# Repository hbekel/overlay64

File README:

overlay64 - video overlay module

The overlay64 module allows superimposing predefined texts onto an
existing composite signal or onto the luminance portion of an s-video
signal depending on the states of up to sixteen digital input
lines. An LM1881 video sync separator IC is used to detect the
vertical and horizontal sync pulses of the video signal. An Atmega1284
uses these signals to synchronize with the video signal and to
superimpose text on the video display by bit-banging the corresponding
characters over SPI.

The user writes a simple configuration file that determines which
texts are to be displayed for which input line states. The
configuration file is converted to a binary format using the supplied
commandline tool before flashing it to the Atmegas's eeprom memory via
the USB interface.

Possible uses include displaying the state of control lines for
additional hardware installed in a homecomputer such as the Commodore
64, for example to display the currently selected kernal based on the
state of the control lines for a multi-kernal adapter.

An early working prototype can be seen in this video where it displays
the runtime configuration of the MixSID Stereo SID board:

https://www.youtube.com/watch?v=0exp2yM0WHM

This repository includes the complete sourcecode of the client
software, the firmware and all design files in KiCAD format.

LICENSING

Hardware licenced under CERN OHL v.1.2, see ./hardware/LICENSE.txt
Software and firmware licenced under GNU GPLv3, see ./LICENSE

The software contains MIT licensed code from
https://github.com/arkku/ihex for reading Intel HEX files, Copyright
(c) 2013-2015 Kimmo Kulovesi, see ./intelhex/LICENSE

The firmware contains the V-USB Driver (https://www.obdev.at/vusb),
(C)2008 Objective Development GmbH.

Distributed in the ./bootloader directory is the USBasp bootloader,
(C)2013 Stephan Baerwolf (matrixstorm@gmx.de) and (C)2008 Objective
Development GmbH (https://www.obdev.at/vusb).

In compliance with the terms of the (identical) V-USB driver and
USBasp bootloader licenses (./firmware/usbdrv/License.txt and
./bootloader/License.txt), the entire project is published under

http://www.henning-bekel.de/overlay64

In addition, this distribution contains

- a circuit diagram in PDF format, see ./hardware/overlay64-schematics.pdf
- the full source code for the host software in ./firmware
- this README file
- references to https://www.obdev.at/vusb

The USB Product and Vendor IDs for the Overlay64 USB device have kindly
been provided by OpenMoko, Inc (http://openmoko.org).

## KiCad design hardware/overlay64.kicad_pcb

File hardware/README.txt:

Overlay64 Rev.1 -- Video Overlay Module
Copyright Henning Bekel 2016.
Licensed under CERN OSH v.1.2 (see LICENSE.pdf)

This directory contains hardware documentation (as defined by the
terms of the CERN OSH v.1.2) for the Overlay64, a simple programmable
video overlay module. For more information, please visit

http://www.henning-bekel.de/overlay64

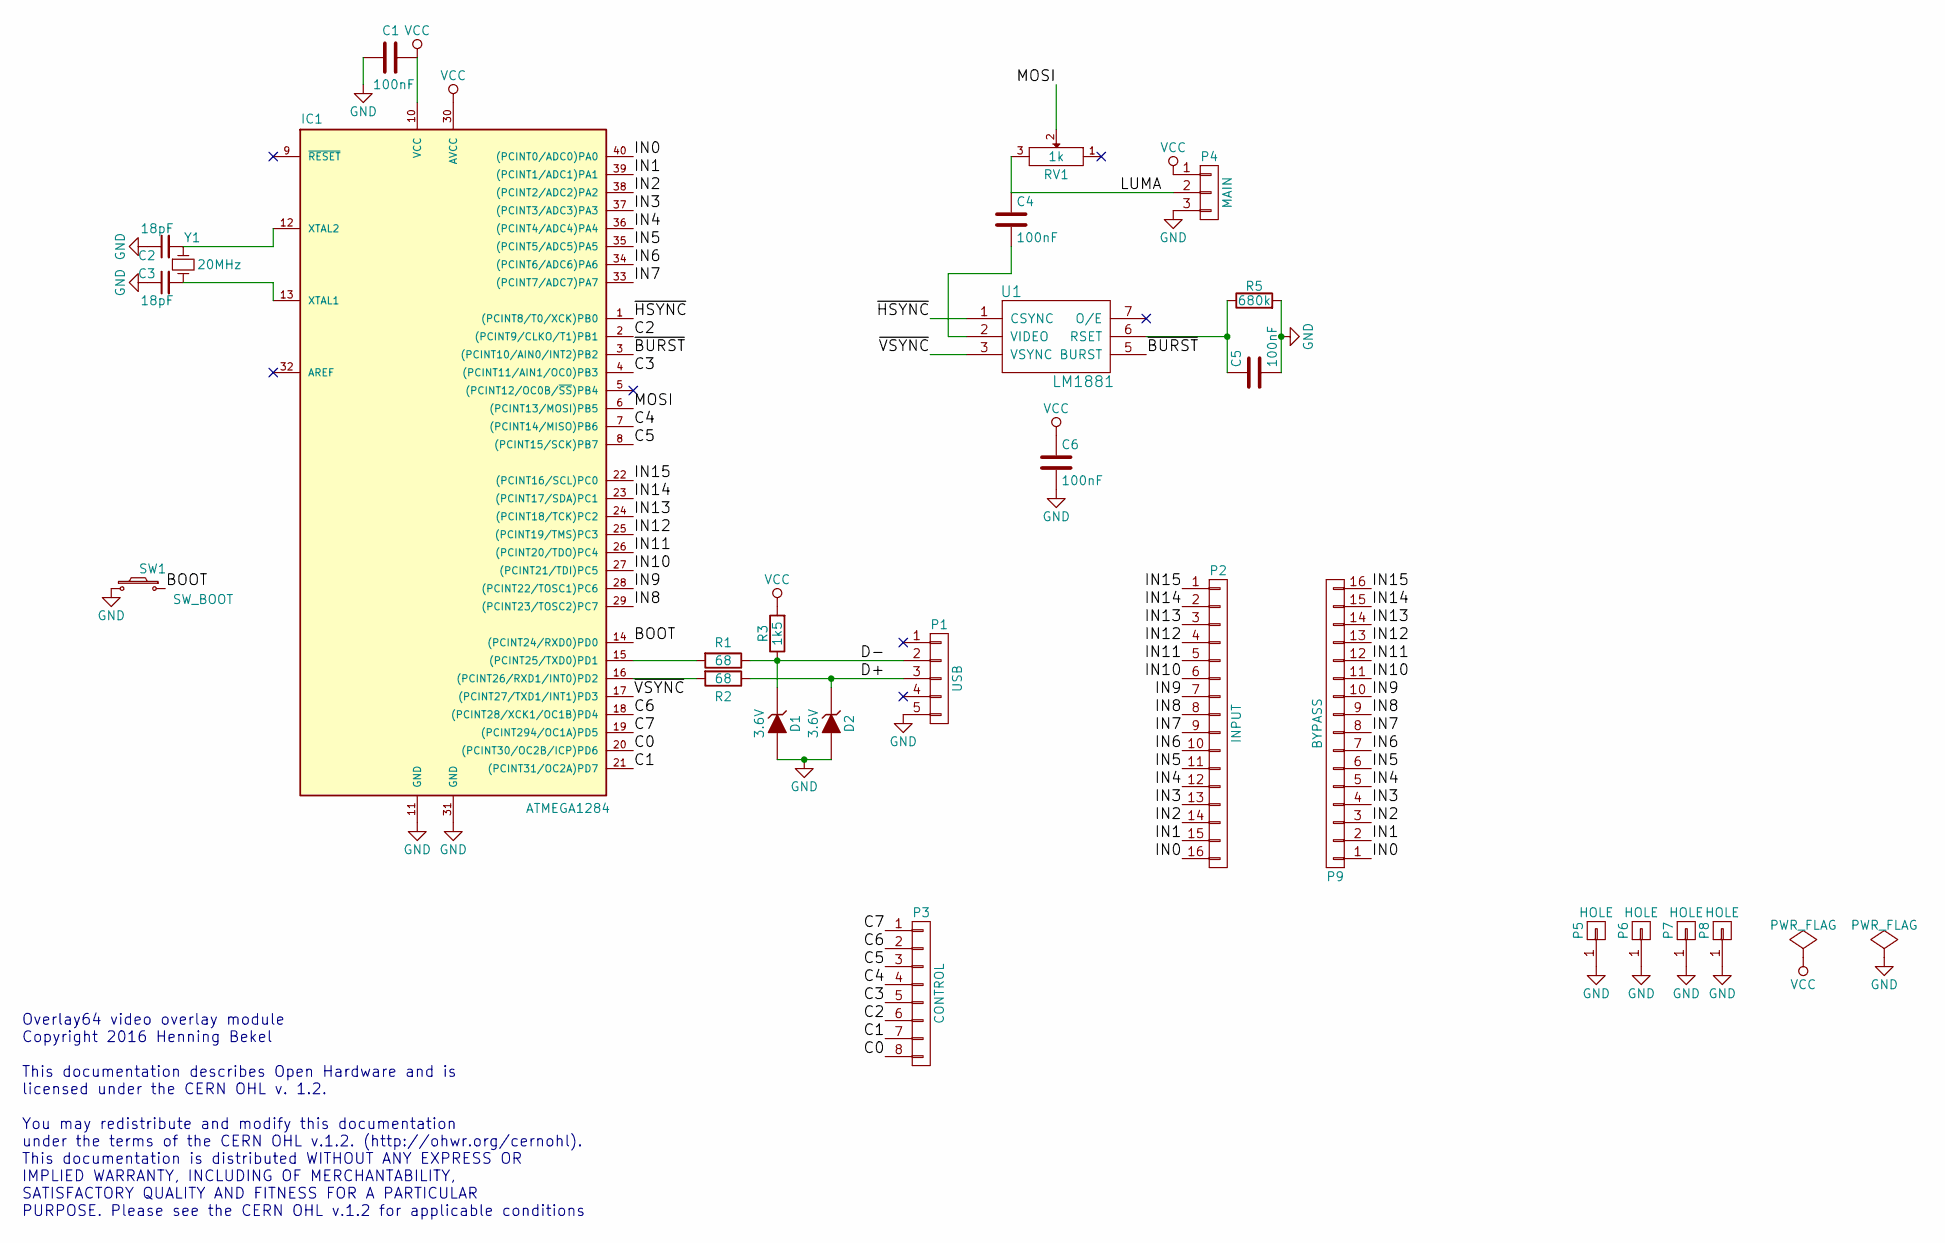
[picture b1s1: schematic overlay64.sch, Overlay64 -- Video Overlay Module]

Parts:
C1, C4, C5, C6: 100nF; C_Disc_D3_P2.5
C2, C3: 18pF; C_Disc_D3_P2.5
D1, D2: 3.6V; D3
IC1: ATMEGA1284; DIP-40_W15.24mm
P1: USB; USB-MINI-B-TH
P2: INPUT; Pin_Header_Angled_1x16
P3: CONTROL; Pin_Header_Angled_1x08
P4: MAIN; Pin_Header_Angled_1x03
P5, P6, P7, P8: HOLE; MountingHole_4mm
P9: BYPASS; Pin_Header_Angled_1x16
R1, R2: 68; R3
R3: 1k5; R3
R5: 680k; R3
RV1: 1k; Potentiometer_Bourns_3339P_Angular_ScrewUp
SW1: SW_BOOT; Button
U1: LM1881; DIP-8_W7.62mm
Y1: 20MHz; Crystal_HC49-U_Vertical

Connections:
/BOOT: IC1.14 ((PCINT24/RXD0)PD0), SW1.2
/C0: IC1.20 ((PCINT30/OC2B/ICP)PD6), P3.8
/C1: IC1.21 ((PCINT31/OC2A)PD7), P3.7
/C2: IC1.2 ((PCINT9/CLKO/T1)PB1), P3.6
/C3: IC1.4 ((PCINT11/AIN1/OC0)PB3), P3.5
/C4: IC1.7 ((PCINT14/MISO)PB6), P3.4
/C5: IC1.8 ((PCINT15/SCK)PB7), P3.3
/C6: IC1.18 ((PCINT28/XCK1/OC1B)PD4), P3.2
/C7: IC1.19 ((PCINT294/OC1A)PD5), P3.1
/D+: D2.1 (K), P1.3, R2.1
/D-: D1.1 (K), P1.2, R1.1, R3.1
/IN0: IC1.40 ((PCINT0/ADC0)PA0), P2.16, P9.1
/IN1: IC1.39 ((PCINT1/ADC1)PA1), P2.15, P9.2
/IN2: IC1.38 ((PCINT2/ADC2)PA2), P2.14, P9.3
/IN3: IC1.37 ((PCINT3/ADC3)PA3), P2.13, P9.4
/IN4: IC1.36 ((PCINT4/ADC4)PA4), P2.12, P9.5
/IN5: IC1.35 ((PCINT5/ADC5)PA5), P2.11, P9.6
/IN6: IC1.34 ((PCINT6/ADC6)PA6), P2.10, P9.7
/IN7: IC1.33 ((PCINT7/ADC7)PA7), P2.9, P9.8
/IN8: IC1.29 ((PCINT23/TOSC2)PC7), P2.8, P9.9
/IN9: IC1.28 ((PCINT22/TOSC1)PC6), P2.7, P9.10
/IN10: IC1.27 ((PCINT21/TDI)PC5), P2.6, P9.11
/IN11: IC1.26 ((PCINT20/TDO)PC4), P2.5, P9.12
/IN12: IC1.25 ((PCINT19/TMS)PC3), P2.4, P9.13
/IN13: IC1.24 ((PCINT18/TCK)PC2), P2.3, P9.14
/IN14: IC1.23 ((PCINT17/SDA)PC1), P2.2, P9.15
/IN15: IC1.22 ((PCINT16/SCL)PC0), P2.1, P9.16
/LUMA: C4.1, P4.2, RV1.3
/MOSI: IC1.6 ((PCINT13/MOSI)PB5), RV1.2
/~BURST: IC1.3 ((PCINT10/AIN0/INT2)PB2), U1.5 (BURST)
/~HSYNC: IC1.1 ((PCINT8/T0/XCK)PB0), U1.1 (CSYNC)
/~VSYNC: IC1.17 ((PCINT27/TXD1/INT1)PD3), U1.3 (VSYNC)
GND: C1.2, C2.1, C3.1, C5.2, C6.2, D1.2 (A), D2.2 (A), IC1.11 (GND), IC1.31 (GND), P1.5, P4.3, P5.1, P6.1, P7.1, P8.1, R5.2, SW1.1, U1.4 (GND)
unnamed: C2.2, IC1.12 (XTAL2), Y1.1
unnamed: C3.2, IC1.13 (XTAL1), Y1.2
unnamed: C4.2, U1.2 (VIDEO)
unnamed: C5.1, R5.1, U1.6 (RSET)
unnamed: IC1.15 ((PCINT25/TXD0)PD1), R1.2
unnamed: IC1.16 ((PCINT26/RXD1/INT0)PD2), R2.2
VCC: C1.1, C6.1, IC1.10 (VCC), IC1.30 (AVCC), P4.1, R3.2, U1.8 (VCC)

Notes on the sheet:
Overlay64 video overlay module Copyright 2016 Henning Bekel This documentation describes Open Hardware and is licensed under the CERN OHL v. 1.2. You may redistribute and modify this documentation under the terms of the CERN OHL v.1.2. (http://ohwr.org/cernohl). This documentation is distributed WI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

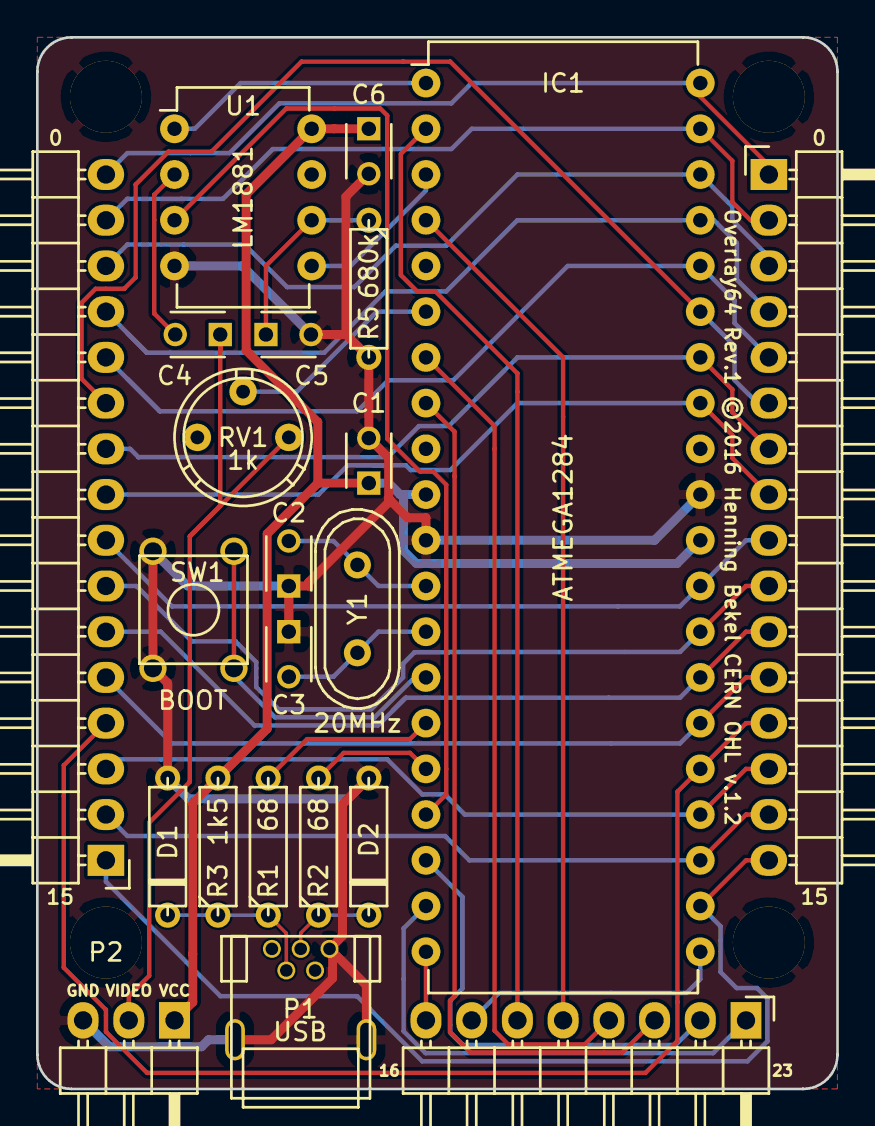
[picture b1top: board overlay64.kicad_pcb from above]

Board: 2 copper layers, 44.5 x 58.4 mm, 26 parts (0 on the bottom side), 40 nets.

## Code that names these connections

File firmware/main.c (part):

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#include "usbdrv/usbdrv.h"
#include "../protocol.h"

#define MOSI (1<<PB5)  // SPI output pin (where the actual bitmap data is send)
#define SS   (1<<PB4)  // SPI slave select (must be pulled up in master mode)

#define ENABLE_SPI  DDRB |= MOSI  // Enable the SPI output pin
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  Config_read(config, &eeprom) || Config_install_fallback(config);

  // Setup INT1, INT2 and PCINT8 pins
  DDRB &= ~(1<<PB2);
  PORTB |= (1<<PB2);

  DDRD &= ~(1<<PD3);
  PORTD |= (1<<PD3); 

  DDRB &= ~(1<<PB0);
  PORTB |= (1<<PB0);
  
  // Setup Interrupts
  EICRA = (1<<ISC11) | (1<<ISC21); // Sense INT1 and INT2 on falling edge
  EIMSK = (1<<INT1);               // Enable interrupt for INT1 (vsync)

  // Setupt Pin Change Interrupt PCINT8 (hsync)
  PCICR = (1<<PCIE1);
  PCMSK1 = (1<<PCINT8);

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ISR(PCINT1_vect, ISR_NOBLOCK) { // HSYNC (each line)...
  
  // Return immediately unless pin has changed to low
  if(PINB & (1<<PB0)) return;

  // When we enter here, there's a jitter of 1-3 cycles due to code
  // executed in the mainloop. Therefore we'll use the BACK PORCH
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
  // Now we're back from INT2_vect, at the end of the line

  // Disable the SPI pin to avoid disturbing the next hsync.
  DISABLE_SPI;
  
  // Disable INT2 (BACK PORCH), enable PCINT1 (HSYNC) again
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//-----------------------------------------------------------------------------

void CheckBootloader(void) {
  DDRD &= ~(1<<PD0);
  PORTD |= (1<<PD0);

  if((PIND & (1<<PD0)) == 0) {
    EnterBootloader();
    Reset();
  }
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
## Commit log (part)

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2016-01-22 Intial commit, rough draft
2016-01-26 Firmware: Switched to atmega328p, added "program" target to Makefile
2016-01-26 Firmware: Added some comments, added macro to convert usecs to cpu cycles
2016-01-27 Firmware: First working implementation, displays "C64" in upper left
2016-01-27 Firmware: Functions to write to the screen and to clear screen regions
2016-01-27 Hardware: Switched to atmega32p, updated to current state on breadboard
2016-01-27 Hardware: Added vic sockets, layed out components (rough draft)
2016-01-27 Firmware: Some premature optimization, code simplified (loops are unrolled)
2016-01-27 Firmware: Some more comments, guessing we'll need one more nop
2016-01-28 Hardware: Removed VIC-Sockets and pcb layout
    Designing this as a VIC-Adpater-board is too complicated, and maybe
    not possible (depending on what the modulator still does to the signal
    to make it a proper C/Y signal).
    It's probably simpler to get LUMA from the connector internally.
2016-01-28 Hardware: Updated schematics, Added /OE, resistor before transistor base
2016-01-29 Software: Designed configuration format and added configuration tool
2016-01-29 Firmware: Setup all user pins as input with pullups
2016-01-29 Firmware: Improved font, centered the characters again
2016-01-31 Firmware: Cde adjustments, auto-disable after 2s, improved font
2016-02-01 Software: Added new overlay.c (main only) missing from last commit
2016-02-01 Firmware: Moved write/clear methods to Row, code cleanups
2016-02-01 Software: Simplified string parsing, allow whitespace, \" and \\
2016-02-02 Firmware: Fixed sparse memory model, expanded screen to 53x30 chars max
    Always allocate a complete row of screen memory for each row used. This
    further speeds up access to the character data, resulting in even smaller
    horizontal gaps between characters.
2016-02-02 Software: Fixed invalid free in Command_parse, fixed footprint calculation
2016-02-02 Software/Firmware: Added configuration command for display timeout
2016-02-02 Firmware: Code cleanups, added more comments
2016-02-02 Software: Report resulting size of binary configuration
2016-02-02 Hardware: Specified correct transistor type (BC547B)
2016-02-02 Firmware: Tristate MOSI for empty lines and outside of the logical screen
2016-02-04 Firmware: Removed pullup on MOSI when disabled (not required)
2016-02-06 Hardware: First draft of pcb layout (rough)
2016-02-06 Firmware: Simplified rendering code
2016-02-08 Firmware: Changed logical port ordering to ease access to first lines
2016-02-08 Software: Improved warnings about used/free eeprom/sram memory
2016-02-08 Hardware: Updated netlist to include OE/OR pins
2016-02-12 Software: Configured for kernal and charset display, addded small font
2016-03-16 Firmware: Some code cleanups and comments added
2016-04-27 Makefile: Added release target
2016-05-24 Hardware: Improved routing
2016-05-24 Hardware: Fixed orientation/wiring for brightness pot
2016-07-21 Firmware/Software: Fixed memory footprint calculation, minor changes
2016-07-27 Project: Added usbasp bootloader
2016-07-28 Software: Adjusted EEPROM/SRAM sizes, normalized config
2016-07-28 Hardware: Corrected OE/OR pins, Software: Disable inputs for now
2016-07-30 Firmware: Adjusted for Atmega1284P, sequential sampling
2016-08-02 Software: Fixed reading of wrong number of input pins from binary config
    This was still hardcoded to 14 pins instead of using the INPUT_PINS
    constant.
2016-08-02 Firmware: Code cleanups, added macros for nops, improved comments
2016-08-02 Hardware: Updated schematics, added BURST signal connection
2016-08-12 Firmware: Some changes to the test config
2016-08-12 Hardware: First draft of new pcb layout, autorouted
2016-08-18 Hardware: Added jumpers for manually entering the bootloader
2016-08-31 Firmware/Software: Added USB device and bootloader command
2016-09-01 Software: Improved Makefile, removed .o files from usbdrv
2016-09-02 Software: Fixed win32 build
2016-09-04 Software/Firmware: Drafting config file format
2016-09-05 Software/Firmware: Added screen struct, improved Makefile
2016-09-06 Software/Firmware: Added control pins to config object
2016-09-07 Software/Firmware: Drafting config file format and application
2016-09-07 Firmware: Fixed some bugs, sample pins only once per pass
2016-09-08 Firmware: Fixed problems with controls/samples/notifications
    When a manual control enables a screen, cancel any pending
    notification for that screen.
    Initially sample the input/control lines, otherwise the first
    sampling is already interpreted as a change, triggering automatic
    screens.
2016-09-08 Firmware: Setup input/control pins according to pin config
2016-09-09 Project: Added Readme
2016-09-09 Project: Updated README
2016-09-17 Software: Adjusted SRAM footprint calculations
2016-10-02 Software/Firmware: Removed distinction between input and control lines
    Now all input pins can be used either as an input line for sampling
    or as a control line. Pins are thus indexed from 0 to 23. The first
    16 lines are the ones passed through on the left and right side, the
    last 8 lines are the ones right of the USB adapter, where pin 16 is
    left and pin 23 is right.
2016-10-05 Software/Firmware: Switched to USB PID/VID kindly provided by OpenMoko, Inc.
2016-11-27 Hardware: Removed backdrop option, single boot button, rerouting...
2016-12-01 Hardware: Added 3d models for button and diodes
2016-12-01 Firmware: Improved bootloader, enter from firmware via magic cookie in eeprom
2016-12-01 Firmware: Added fallback configuration in case of empty eeprom
    The fallback configuration simply displays some information
    when no valid configuation is found in eeprom memory. This will
    most likely be the case when the device is powered on for the
    first time.
2016-12-02 Software: Added identify command, reports remote firmware version
2016-12-02 Software: Update from .hex files, single file argument implies configure
    Firmware can now be updated from an Intel HEX file as well, format
    determined by file extension .hex
    When the sole command line argument is a filename, use that file as
    configuration to parse and transfer.
2016-12-03 Project: Hardware documentation licensed under CERN OHL 1.2
2016-12-03 Documentation: Added schematics plot in svg format
2016-12-06 Project: Added sources and Makefile to build ihex2bin
2016-12-06 Software: Improved error messages for missing USB devices
2016-12-06 Hardware: Added rendering of component placement
2016-12-06 Makefile: Added udev rule installation for linux
2016-12-06 Software: Removed superfluous Pin_free() in Control_free()
    Pins are managed by Config only. For some reason this only caused
    a seqfault for Config_free() with native cygwin builds.
2016-12-08 Software: Output usage on unknown command and/or wrong numer of args
2016-12-08 Makefile: Improved zip filename for gerber files, include in release
2016-12-08 Hardware: Updated gerber files for revision 1
2016-12-09 Firmware: Fixed font bug introduced with last commit
2016-12-10 Software/Firmware: Added "font" command to flash alternative font
    The firmware needs to be rebuild and updated for this to work.
    overlay64 font <infile>
    The input file is a binary font image similar to a C64 rom image.
    Only the first 96 characters are flashed, corresponding to the
    ascii characters 32-127.
    To convert an existing C64 font (which has a different order),
2016-12-11 Software: Added command to convert c64 charsets to overlayt64 fonts
    $ overlay64 font-convert <infile> <outfile>
    $ overlay64 font-update <infile>
    The "font-convert" command converts a C64 charset image to an
    overlay64 font file.
    The "font" command has been renamed to "font-update" (transfer
    an overlay64 font file to the device).
2016-12-11 Project: Added some alternative charsets
2016-12-12 Software: Improved help messages
2016-12-14 Software: fixed wrong usage message after convert (missing else)
2016-12-15 Software: Removed --device option, not required for this device
2016-12-16 Hardware: Updated rendering of component placement
2016-12-20 Makefiles: Improved sh-compatibility
2016-12-20 Makefiles: Removed informative avr-size calls
    The bootloader Makefiles contain informative calls to avr-size which
    rely on a patched version of avr-size adding the non-standard --mcu
    option. Most distributions add this patch, but not all of them.
2017-01-06 Software: Fixed bugs in parsing/reading clear commands
2017-01-27 Software/Firmware: Improved display logic, improved flashing, bugfixes
    Improved screen logic. Independent of the screen or control mode,
    a screen is only enabled if at least one write command is found
    to be effective. This can either be an unconditional write command
    or a write command depending on a certain input line state.
    In addition, a sample does not need to cover all possible input
    line states anymore.
2017-01-30 Software: Fixed # in string literals, fixes issue #1
2017-01-31 Firmware: Assure bootloader flag is cleared before reset
2017-02-03 Software: Improved parsing, error handling, eased contstraints
2017-02-21 Version 1.1
2017-04-11 Firmware: Improved chances of proper device enumeration for some Windows versions.
    It appears that on some Windows versions and/or installations device
    enumeration may fail due to Windows giving up on enumeration too early.
    A workaround for the current 1.1 version of the firmware is to disconnect
    the cable from the PC when the device is powered on and to connect
    it to the PC after a few seconds.
    Thus the previously introduced delay has been removed again. Note
2017-04-11 Firmware: Added additional firmware bootloader check on powerup/reset
2017-04-15 Overlay64: Added bash completion support
2017-04-18 Software: Fixed build errors on OSX (missing fmemopen)
    Also removed some warnings when building with clang.
2017-04-20 Firmware: Fixed wrong USB vendor name length in usbconfig.h
2017-05-06 Software: Fixed bug parsing strings containing equal sign
2017-07-22 Firmware: Fixed slightly skewed first text lines on some monitors
    On some monitors, the display of the first text line may have been
    slightly skewed due to the fact that the SPI line was simply left
    enabled and low throughout the next hsync. Whether or not this
    effect is noticiable seems to depend on the actual input impedance
    of the monitor in use. The SPI line is now tristated after every
    rendered scanline, shortly before the next hsync occurs.
2017-09-16 Fixed bug in screen parsing for unconditional writes containing equal signs
    Reported by Markus Jentsch
2017-11-05 Improved update command for updates that break binary compatibility
    The update command now accepts a configuration file as a second optional
    argument. If specified, the exisitng configuration on the device will be
    erased before updating the firmware and recreated and reflashed after the
    update. This prevents the new firmware from crashing when trying to read
    a deprecated binary configuration format still present on the device.

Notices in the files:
firmware/main.c:
This program is free software: you can redistribute it and/or modify
it under the terms of the GNU General Public License as published by
the Free Software Foundation, either version 3 of the License, or
(at your option) any later version.
hardware/overlay64.kicad_pcb:
Licensed under CERN OHL v.1.2
Overlay64 Rev.1 ©2016 Henning Bekel CERN OHL v.1.2
